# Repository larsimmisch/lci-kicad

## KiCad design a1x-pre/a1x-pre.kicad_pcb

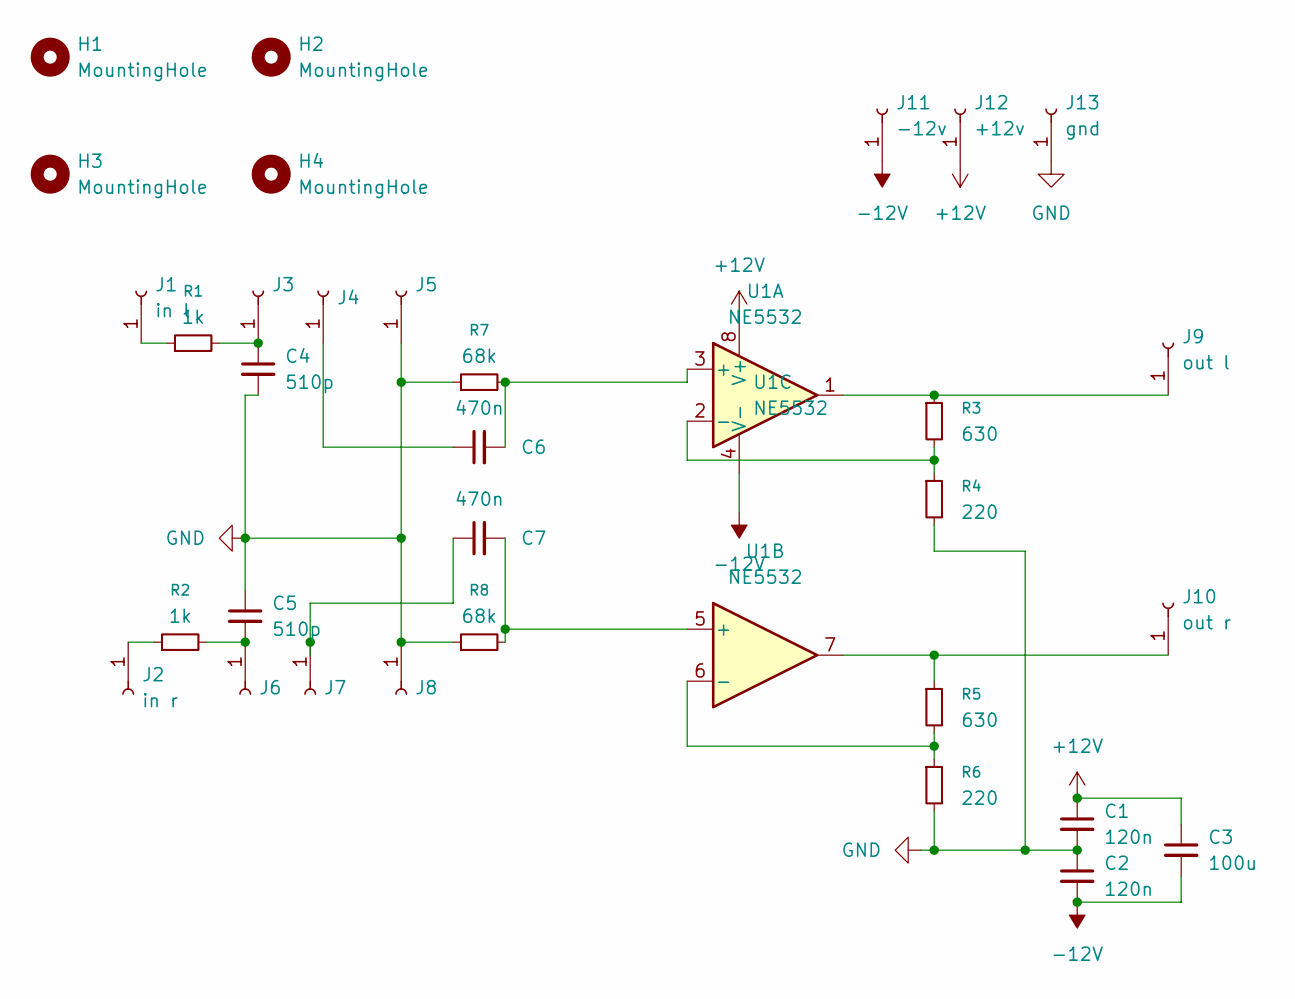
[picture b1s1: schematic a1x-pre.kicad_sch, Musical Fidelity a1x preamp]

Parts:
C1, C2: 120n; C_0201_0603Metric_Pad0.64x0.40mm_HandSolder
C3: 100u; C_0201_0603Metric_Pad0.64x0.40mm_HandSolder
C4, C5: 510p; C_0201_0603Metric_Pad0.64x0.40mm_HandSolder
C6, C7: 470n; C_0201_0603Metric_Pad0.64x0.40mm_HandSolder
H1, H2, H3, H4: MountingHole; MountingHole_3.2mm_M3
J1: in l; PinHeader_1x01_P1.00mm_Vertical
J2: in r; PinHeader_1x01_P1.00mm_Vertical
J3, J4, J5, J6, J7, J8: Conn_01x01_Socket; PinHeader_1x01_P1.00mm_Vertical
J9: out l; PinHeader_1x01_P1.00mm_Vertical
J10: out r; PinHeader_1x01_P1.00mm_Vertical
J11: -12v; PinHeader_1x01_P1.00mm_Vertical
J12: +12v; PinHeader_1x01_P1.00mm_Vertical
J13: gnd; PinHeader_1x01_P1.00mm_Vertical
R1, R2: 1k; R_0201_0603Metric_Pad0.64x0.40mm_HandSolder
R3, R5: 630; R_0201_0603Metric_Pad0.64x0.40mm_HandSolder
R4, R6: 220; R_0201_0603Metric_Pad0.64x0.40mm_HandSolder
R7, R8: 68k; R_0201_0603Metric_Pad0.64x0.40mm_HandSolder
U1: NE5532; SOIC-8_3.9x4.9mm_P1.27mm

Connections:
+12V: C1.1, C3.1, J12.1, U1.8 (V+)
-12V: C2.2, C3.2, J11.1, U1.4 (V-)
GND: C1.2, C2.1, C4.2, C5.1, J5.1, J8.1, J13.1, R4.2, R6.2, R7.1, R8.1
unnamed: J1.1, R1.1
unnamed: J2.1, R2.1
unnamed: C4.1, J3.1, R1.2
unnamed: C6.1, J4.1
unnamed: C5.2, J6.1, R2.2
unnamed: C7.1, J7.1
unnamed: J9.1, R3.1, U1.1
unnamed: J10.1, R5.1, U1.7
unnamed: C6.2, R7.2, U1.3 (+)
unnamed: R3.2, R4.1, U1.2 (-)
unnamed: C7.2, R8.2, U1.5 (+)
unnamed: R5.2, R6.1, U1.6 (-)

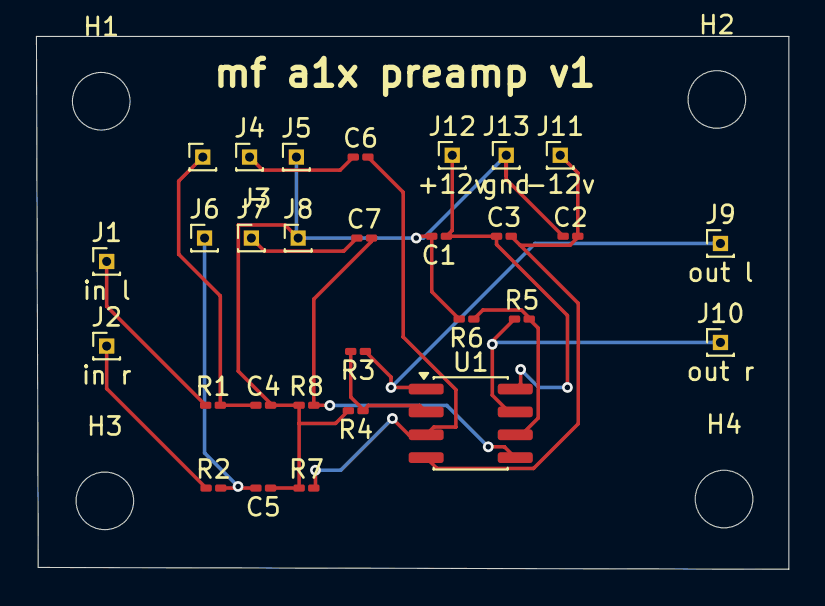
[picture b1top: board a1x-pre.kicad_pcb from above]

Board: 2 copper layers, 41.8 x 29.6 mm, 33 parts (0 on the bottom side), 15 nets.

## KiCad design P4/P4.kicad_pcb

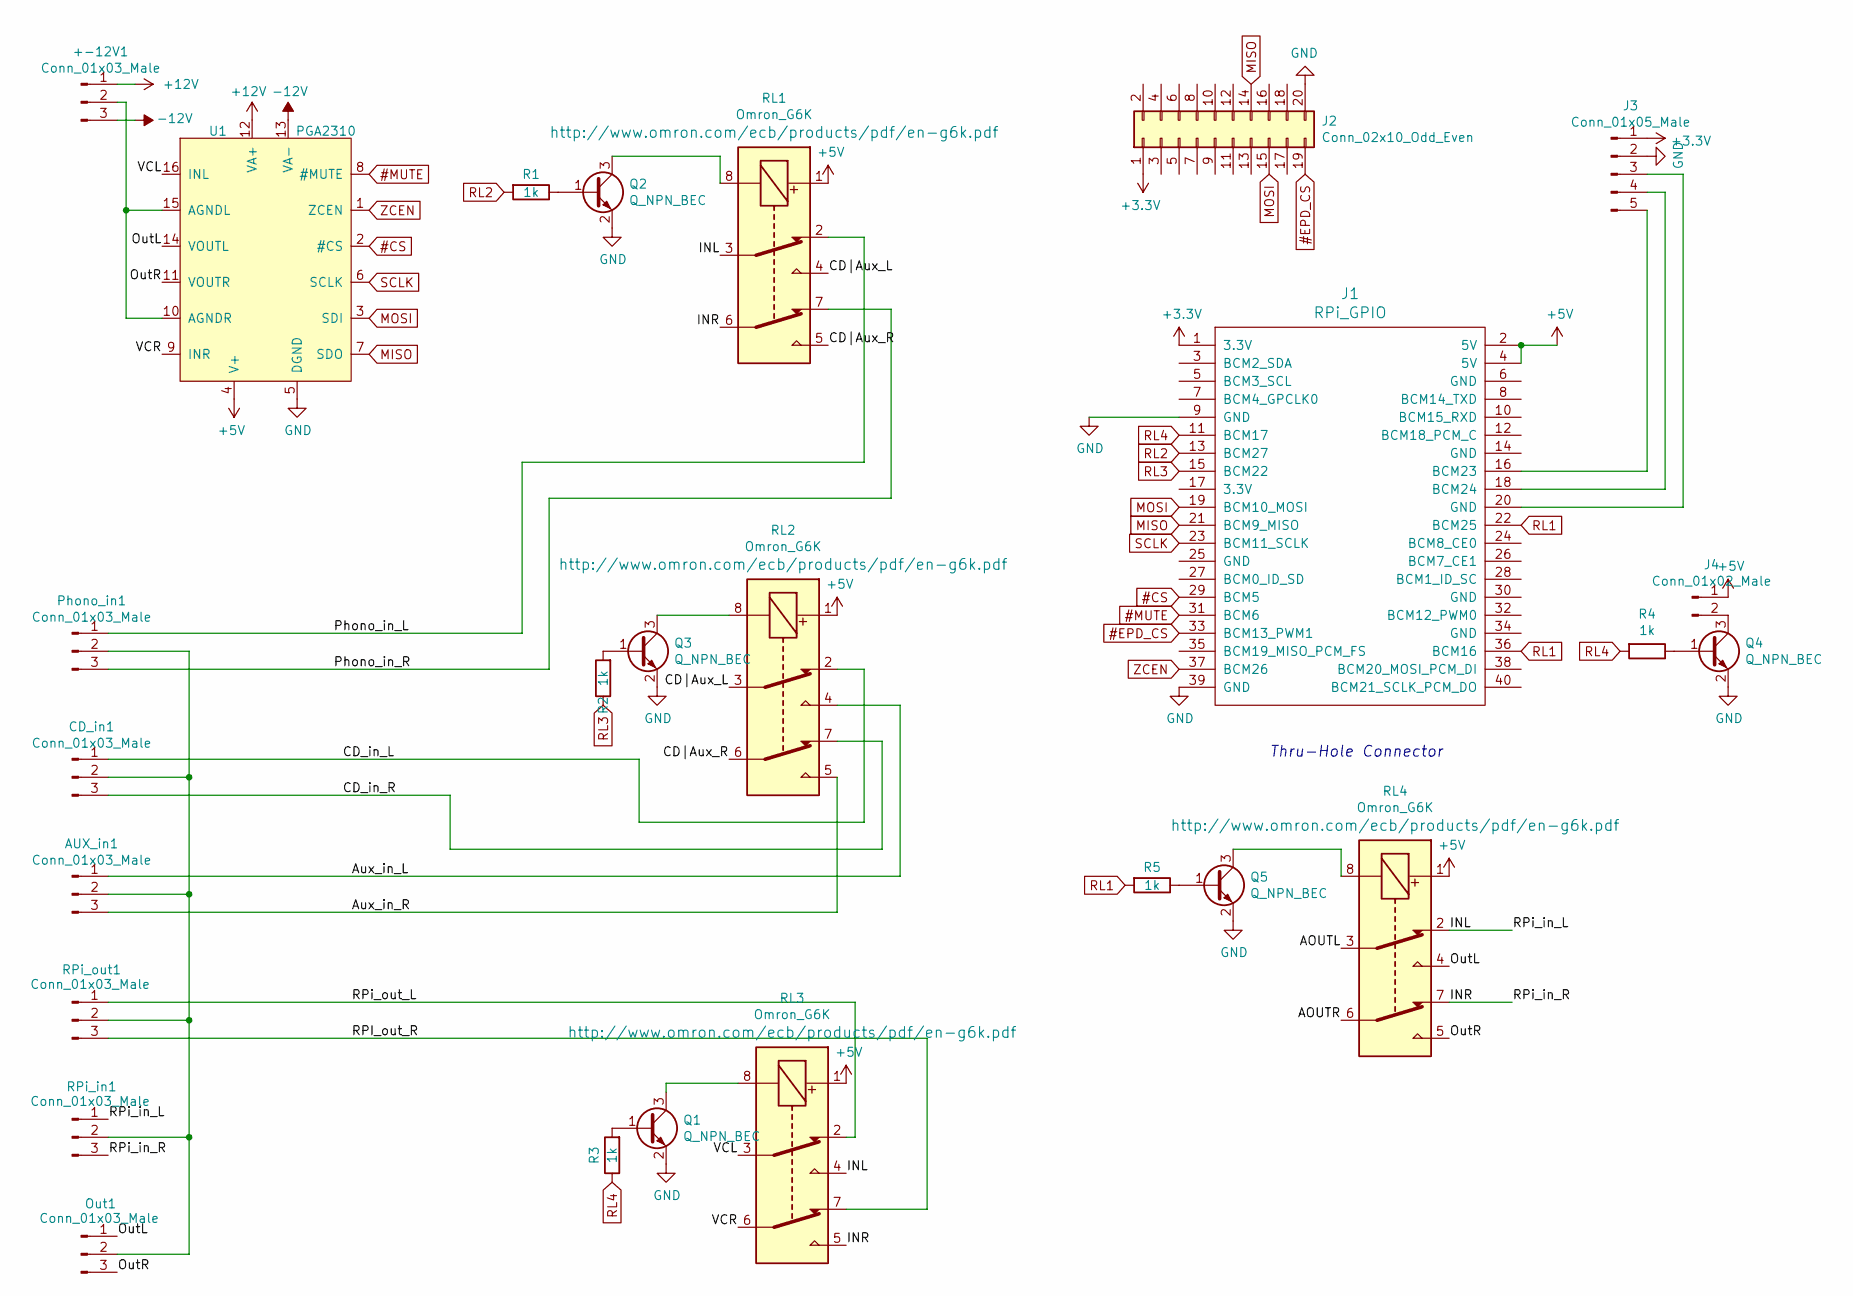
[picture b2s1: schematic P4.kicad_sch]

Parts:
+-12V1: Conn_01x03_Male; PinSocket_1x03_P2.54mm_Vertical
AUX_in1: Conn_01x03_Male; PinSocket_1x03_P2.54mm_Vertical
CD_in1: Conn_01x03_Male; PinSocket_1x03_P2.54mm_Vertical
J1: RPi_GPIO; PinHeader_2x20_P2.54mm_Vertical
J2: Conn_02x10_Odd_Even; PinHeader_2x10_P2.54mm_Vertical
J3: Conn_01x05_Male; PinSocket_1x05_P2.54mm_Vertical
J4: Conn_01x02_Male; PinSocket_1x02_P2.54mm_Vertical
Out1: Conn_01x03_Male; PinSocket_1x03_P2.54mm_Vertical
Phono_in1: Conn_01x03_Male; PinSocket_1x03_P2.54mm_Vertical
Q1, Q2, Q3, Q4, Q5: Q_NPN_BEC; SOT-23W_Handsoldering
R1, R2, R3, R4, R5: 1k; R_0603_1608Metric_Pad0.98x0.95mm_HandSolder
RL1, RL2, RL3, RL4: Omron_G6K; Relay_DPDT_Omron_G6K-2F
RPi_in1: Conn_01x03_Male; PinSocket_1x03_P2.54mm_Vertical
RPi_out1: Conn_01x03_Male; PinSocket_1x03_P2.54mm_Vertical
U1: PGA2310; SOIC-16W_7.5x10.3mm_P1.27mm

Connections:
#CS: J1.29 (BCM5), U1.2 (#CS)
#EPD_CS: J1.33 (BCM13_PWM1), J2.19
#MUTE: J1.31 (BCM6), U1.8 (#MUTE)
+3.3V: J1.1 (3.3V), J2.1, J3.1
+5V: J1.2 (5V), J1.4 (5V), J4.1, RL1.1, RL2.1, RL3.1, RL4.1, U1.4 (V+)
+12V: +-12V1.1, U1.12 (VA+); also elsewhere on the board
-12V: +-12V1.3, U1.13 (VA-); also elsewhere on the board
/AOUTL: RL4.3
/AOUTR: RL4.6
/Aux_in_L: AUX_in1.1, RL2.4
/Aux_in_R: AUX_in1.3, RL2.5
/CD_in_L: CD_in1.1, RL2.2
/CD_in_R: CD_in1.3, RL2.7
/CD|Aux_L: RL1.4, RL2.3
/CD|Aux_R: RL1.5, RL2.6
/INL: RL1.3, RL3.4, RL4.2, RPi_in1.1
/INR: RL1.6, RL3.5, RL4.7, RPi_in1.3
/OutL: Out1.1, RL4.4, U1.14 (VOUTL)
/OutR: Out1.3, RL4.5, U1.11 (VOUTR)
/Phono_in_L: Phono_in1.1, RL1.2
/Phono_in_R: Phono_in1.3, RL1.7
/RPI_out_R: RL3.7, RPi_out1.3
/RPi_out_L: RL3.2, RPi_out1.1
/VCL: RL3.3, U1.16 (INL)
/VCR: RL3.6, U1.9 (INR)
GND: J1.9 (GND), J1.39 (GND), J2.20, J3.2, Q1.2 (E), Q2.2 (E), Q3.2 (E), Q4.2 (E), Q5.2 (E), U1.5 (DGND)
MISO: J1.21 (BCM9_MISO), J2.14, U1.7 (SDO)
MOSI: J1.19 (BCM10_MOSI), J2.15, U1.3 (SDI)
unnamed 28: +-12V1.2, U1.10 (AGNDR), U1.15 (AGNDL); also elsewhere on the board
unnamed: AUX_in1.2, CD_in1.2, Out1.2, Phono_in1.2, RPi_in1.2, RPi_out1.2
unnamed: J1.16 (BCM23), J3.5
unnamed: J1.18 (BCM24), J3.4
unnamed: J1.20 (GND), J3.3
unnamed: J4.2, Q4.3 (C)
unnamed: Q1.1 (B), R3.2
unnamed: Q1.3 (C), RL3.8
unnamed: Q2.1 (B), R1.1
unnamed: Q2.3 (C), RL1.8
unnamed: Q3.1 (B), R2.2
unnamed: Q3.3 (C), RL2.8
unnamed: Q4.1 (B), R4.1
unnamed: Q5.1 (B), R5.1
unnamed: Q5.3 (C), RL4.8
RL1: J1.22 (BCM25), J1.36 (BCM16), R5.2
RL2: J1.13 (BCM27), R1.2
RL3: J1.15 (BCM22), R2.1
RL4: J1.11 (BCM17), R3.1, R4.2
SCLK: J1.23 (BCM11_SCLK), U1.6 (SCLK)
ZCEN: J1.37 (BCM26), U1.1 (ZCEN)

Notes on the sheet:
Thru-Hole Connector

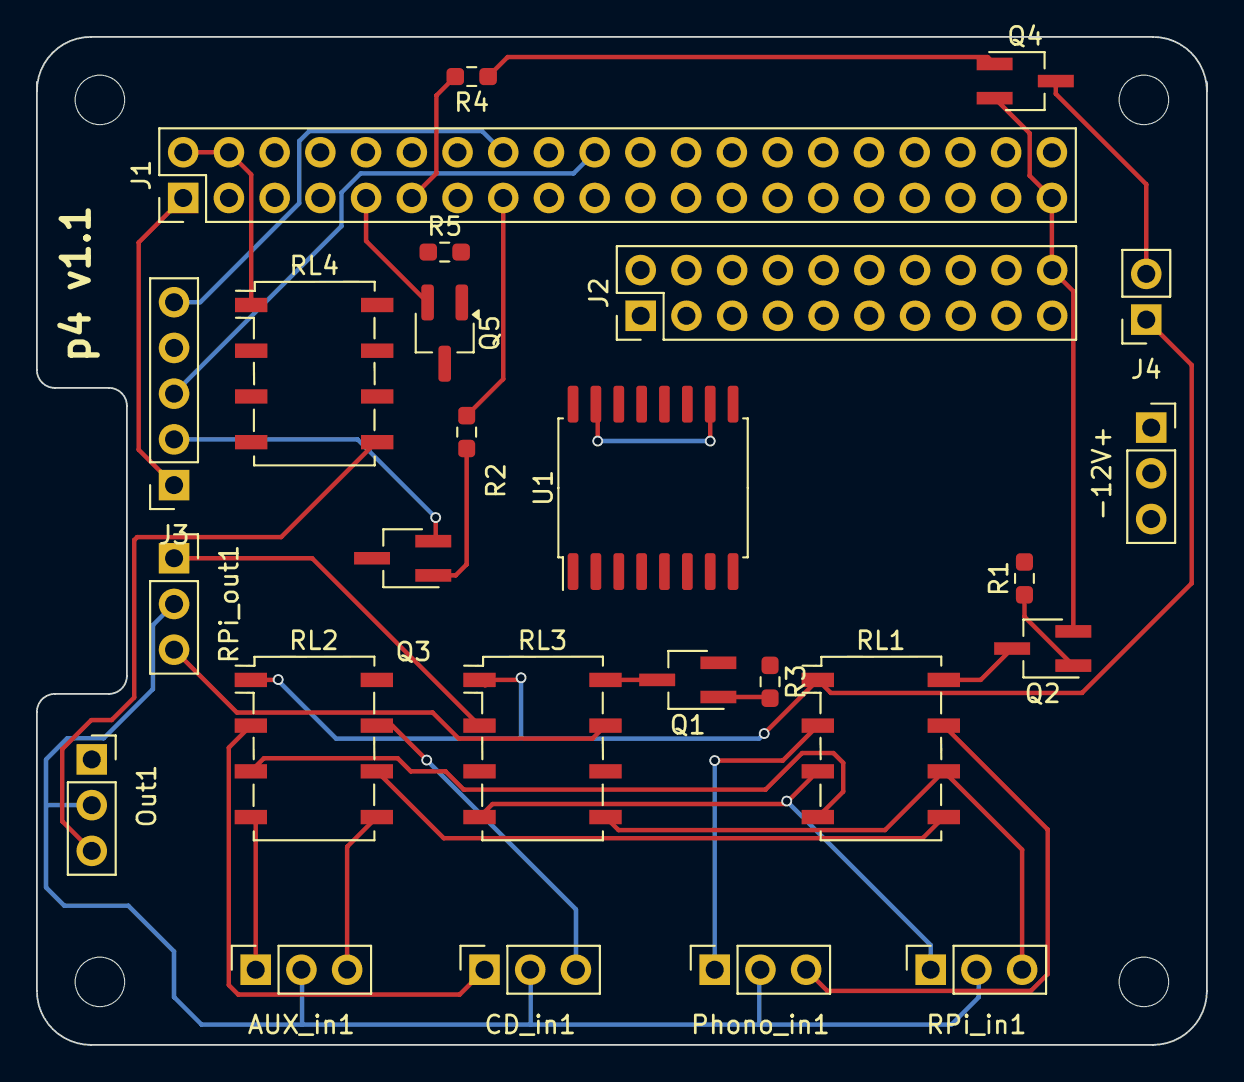
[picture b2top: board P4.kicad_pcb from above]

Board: 2 copper layers, 65.0 x 56.0 mm, 26 parts (0 on the bottom side), 47 nets.

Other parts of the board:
-12V+: Conn_01x03_Male; PinSocket_1x03_P2.54mm_Vertical

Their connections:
+12V: -12V+.1; also elsewhere on the board
-12V: -12V+.3; also elsewhere on the board
unnamed 28: -12V+.2; also elsewhere on the board

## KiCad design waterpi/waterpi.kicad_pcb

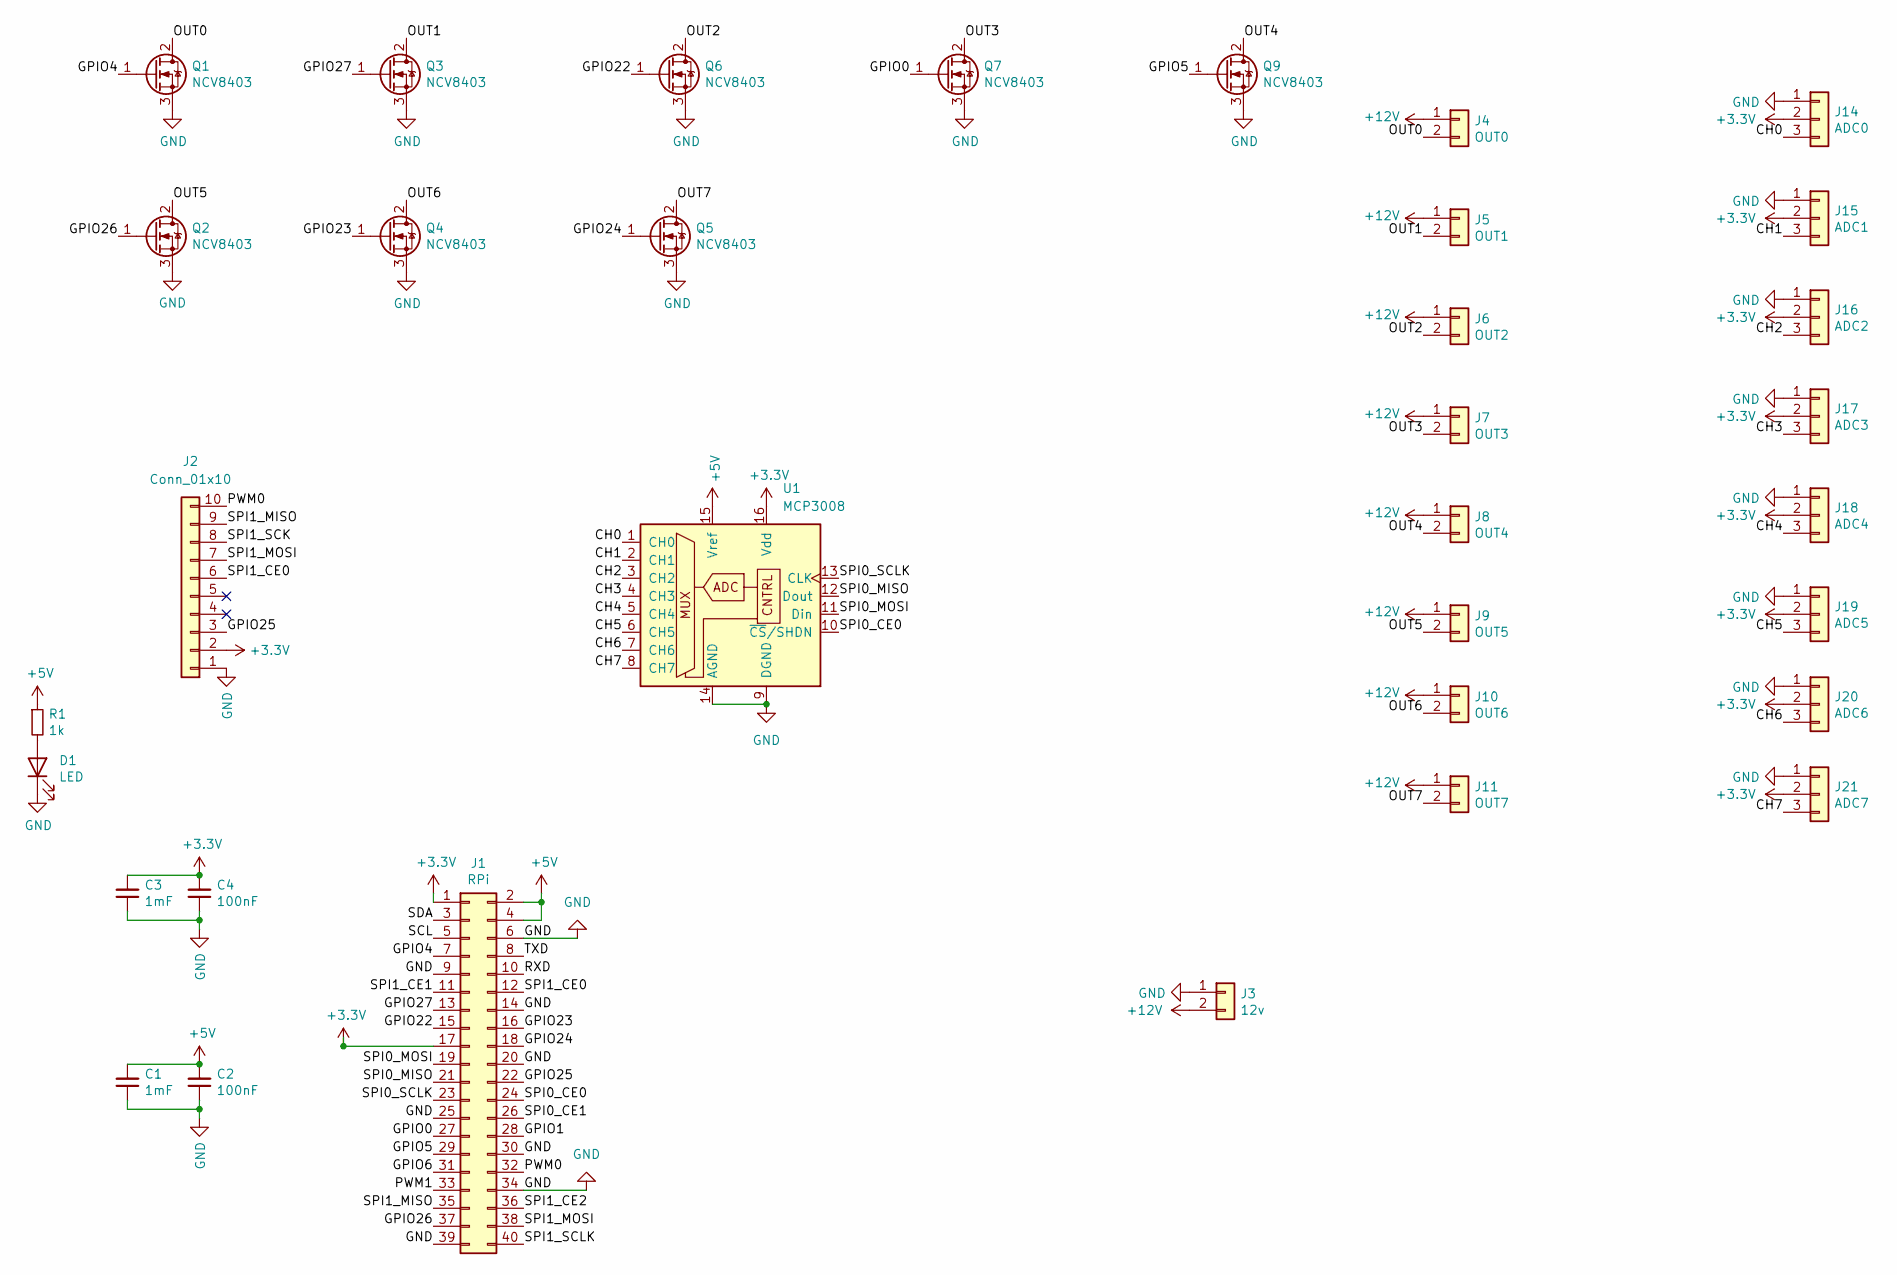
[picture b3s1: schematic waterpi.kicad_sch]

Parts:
C1, C3: 1mF; C_Rect_L4.0mm_W2.5mm_P2.50mm
C2, C4: 100nF; C_0603_1608Metric_Pad1.08x0.95mm_HandSolder
D1: LED; LED_0603_1608Metric_Pad1.05x0.95mm_HandSolder
J1: RPi; PinSocket_2x20_P2.54mm_Vertical
J2: Conn_01x10; PinSocket_1x10_P2.54mm_Vertical
J3: 12v; PinSocket_1x02_P2.54mm_Vertical
J4: OUT0; PinSocket_1x02_P2.54mm_Vertical
J5: OUT1; PinSocket_1x02_P2.54mm_Vertical
J6: OUT2; PinSocket_1x02_P2.54mm_Vertical
J7: OUT3; PinSocket_1x02_P2.54mm_Vertical
J8: OUT4; PinSocket_1x02_P2.54mm_Vertical
J9: OUT5; PinSocket_1x02_P2.54mm_Vertical
J10: OUT6; PinSocket_1x02_P2.54mm_Vertical
J11: OUT7; PinSocket_1x02_P2.54mm_Vertical
J14: ADC0; PinHeader_1x03_P2.54mm_Vertical
J15: ADC1; PinHeader_1x03_P2.54mm_Vertical
J16: ADC2; PinHeader_1x03_P2.54mm_Vertical
J17: ADC3; PinHeader_1x03_P2.54mm_Vertical
J18: ADC4; PinHeader_1x03_P2.54mm_Vertical
J19: ADC5; PinHeader_1x03_P2.54mm_Vertical
J20: ADC6; PinHeader_1x03_P2.54mm_Vertical
J21: ADC7; PinHeader_1x03_P2.54mm_Vertical
Q1, Q2, Q3, Q4, Q5, Q6, Q7, Q9: NCV8403; SOT-223-3_TabPin2
R1: 1k; R_0603_1608Metric_Pad1.05x0.95mm_HandSolder
U1: MCP3008; SO-16_3.9x9.9mm_P1.27mm

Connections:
+3.3V: C3.2, C4.2, J1.1, J1.17, J2.2, J14.2, J15.2, J16.2, J17.2, J18.2, J19.2, J20.2, J21.2, U1.16 (Vdd)
+5V: C1.2, C2.2, J1.2, J1.4, R1.1, U1.15 (Vref)
+12V: J3.2, J4.1, J5.1, J6.1, J7.1, J8.1, J9.1, J10.1, J11.1
/CH0: J14.3, U1.1 (CH0)
/CH1: J15.3, U1.2 (CH1)
/CH2: J16.3, U1.3 (CH2)
/CH3: J17.3, U1.4 (CH3)
/CH4: J18.3, U1.5 (CH4)
/CH5: J19.3, U1.6 (CH5)
/CH6: J20.3, U1.7 (CH6)
/CH7: J21.3, U1.8 (CH7)
/GPIO0: J1.27, Q7.1 (G)
/GPIO1: J1.28
/GPIO4: J1.7, Q1.1 (G)
/GPIO5: J1.29, Q9.1 (G)
/GPIO6: J1.31
/GPIO22: J1.15, Q6.1 (G)
/GPIO23: J1.16, Q4.1 (G)
/GPIO24: J1.18, Q5.1 (G)
/GPIO25: J1.22, J2.3
/GPIO26: J1.37, Q2.1 (G)
/GPIO27: J1.13, Q3.1 (G)
/OUT0: J4.2, Q1.2 (D)
/OUT1: J5.2, Q3.2 (D)
/OUT2: J6.2, Q6.2 (D)
/OUT3: J7.2, Q7.2 (D)
/OUT4: J8.2, Q9.2 (D)
/OUT5: J9.2, Q2.2 (D)
/OUT6: J10.2, Q4.2 (D)
/OUT7: J11.2, Q5.2 (D)
/PWM0: J1.32, J2.10
/PWM1: J1.33
/RXD: J1.10
/SCL: J1.5
/SDA: J1.3
/SPI0_CE0: J1.24, U1.10 (~CS/SHDN)
/SPI0_CE1: J1.26
/SPI0_MISO: J1.21, U1.12 (Dout)
/SPI0_MOSI: J1.19, U1.11 (Din)
/SPI0_SCLK: J1.23, U1.13 (CLK)
/SPI1_CE0: J1.12, J2.6
/SPI1_CE1: J1.11
/SPI1_CE2: J1.36
/SPI1_MISO: J1.35, J2.9
/SPI1_MOSI: J1.38, J2.7
/SPI1_SCK: J2.8
/SPI1_SCLK: J1.40
/TXD: J1.8
GND: C1.1, C2.1, C3.1, C4.1, D1.1 (K), J1.6, J1.9, J1.14, J1.20, J1.25, J1.30, J1.34, J1.39, J2.1, J3.1, J14.1, J15.1, J16.1, J17.1, J18.1, J19.1, J20.1, J21.1, Q1.3 (S), Q2.3 (S), Q3.3 (S), Q4.3 (S), Q5.3 (S), Q6.3 (S), Q7.3 (S), Q9.3 (S), U1.9 (DGND), U1.14 (AGND)
unnamed: D1.2 (A), R1.2

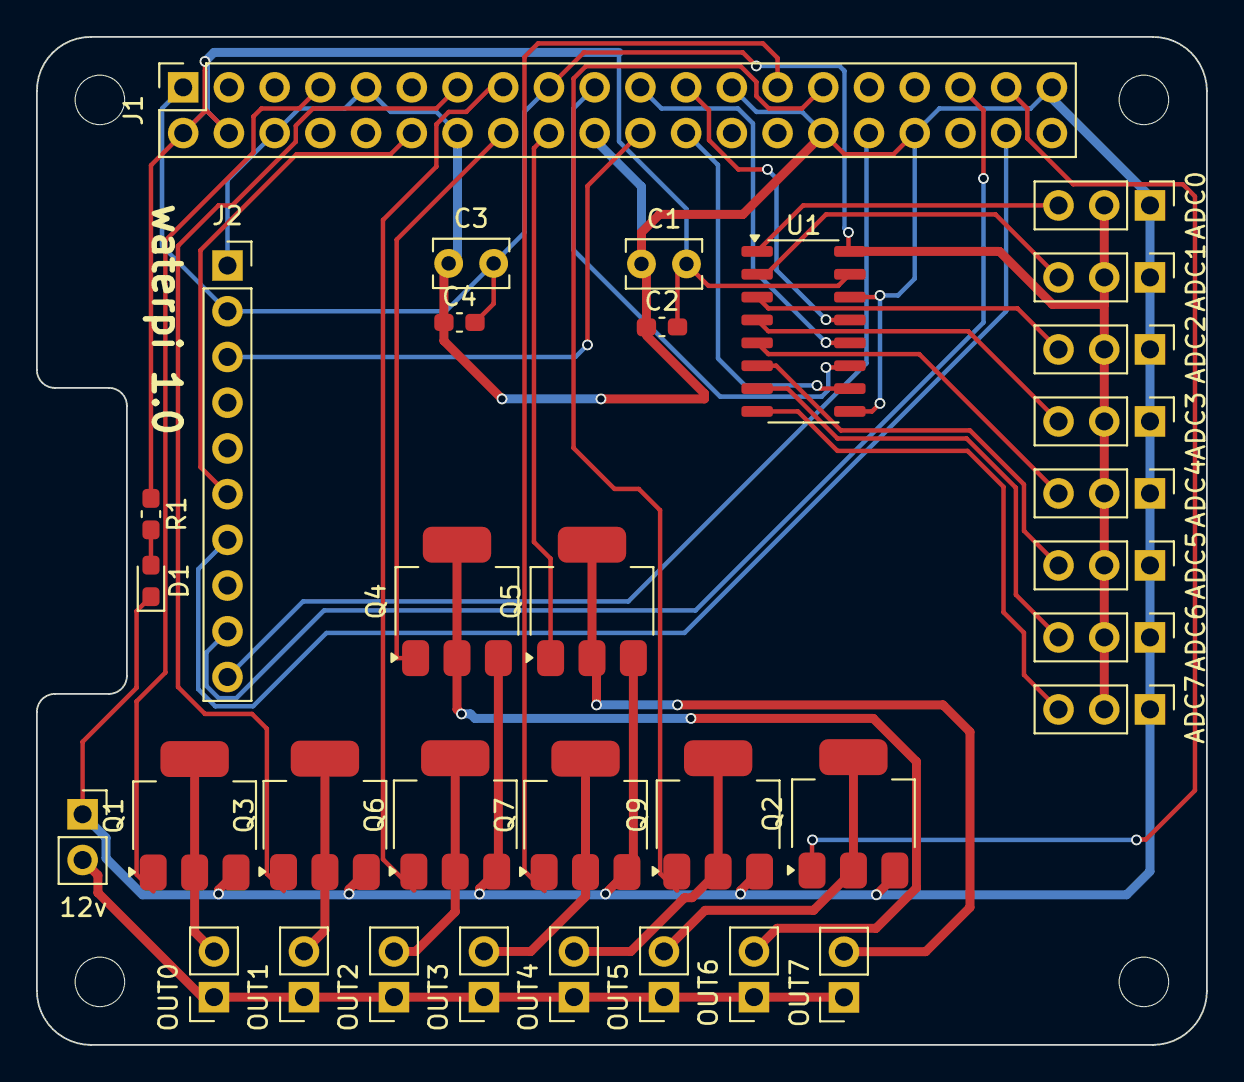
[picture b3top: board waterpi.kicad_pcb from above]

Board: 2 copper layers, 65.0 x 56.0 mm, 34 parts (0 on the bottom side), 38 nets.

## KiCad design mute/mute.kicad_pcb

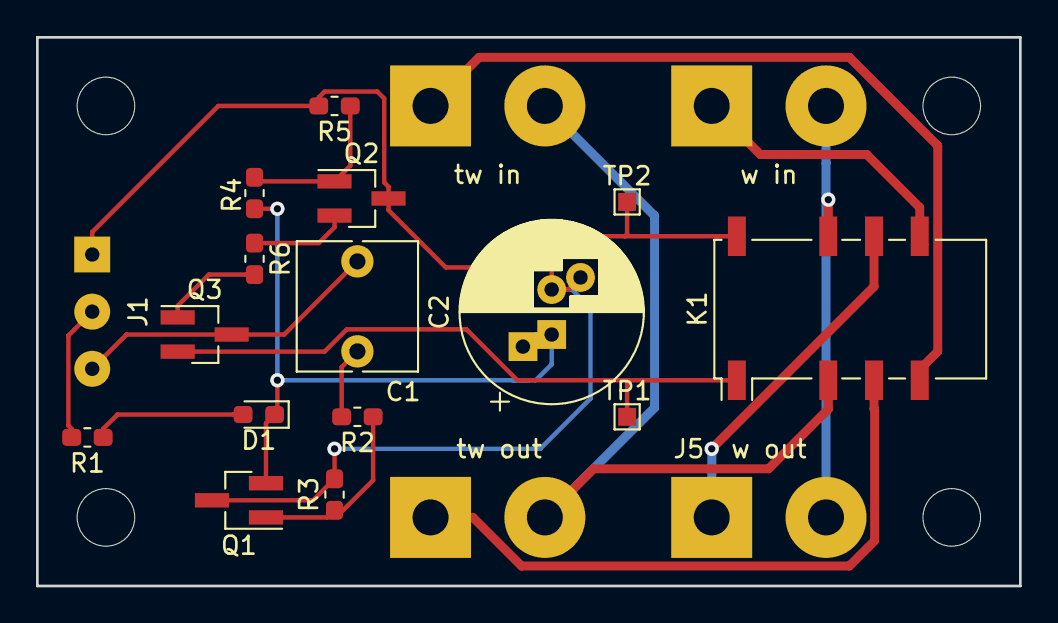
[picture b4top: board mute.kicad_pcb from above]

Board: 2 copper layers, 54.6 x 30.5 mm, 24 parts (0 on the bottom side), 17 nets.

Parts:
C1: 100n; C_Rect_L7.0mm_W6.5mm_P5.00mm
C2: 3.3u; CP_Radial_D10.0mm_P2.50mm_P5.00mm
D1: D; D_0603_1608Metric_Pad1.05x0.95mm_HandSolder
H1, H2, H3, H4: MountingHole; MountingHole_3.2mm_M3_ISO7380
J1: Conn_01x03; SolderWirePad_1x03_P3.175mm_Drill0.8mm
J2: tw in; SolderWirePad_1x02_P7.62mm_Drill2mm
J3: tw out; SolderWirePad_1x02_P7.62mm_Drill2mm
J4: w in; SolderWirePad_1x02_P7.62mm_Drill2mm
J5: w out; SolderWirePad_1x02_P7.62mm_Drill2mm
K1: G6S-2; Relay_DPDT_Omron_G6S-2F
Q1, Q2: npn; SOT-23_Handsoldering
Q3: pnp; SOT-23_Handsoldering
R1, R2, R4, R5, R6: 10k; R_0603_1608Metric_Pad1.05x0.95mm_HandSolder
R3: 100k; R_0603_1608Metric_Pad1.05x0.95mm_HandSolder
TP1, TP2: TestPoint; TestPoint_Pad_1.0x1.0mm

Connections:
/ACSense: J1.2, R1.2
/Aux: K1.1, Q3.2, TP1.1
GND: C2.2, J1.1, K1.12, Q1.3, Q2.3, R3.2, R5.2, TP2.1
unnamed: C1.1, J1.3, Q3.3
unnamed: C1.2, R2.2
unnamed: C2.1, D1.1, Q1.2, R4.2
unnamed: D1.2, R1.1
unnamed: J2.1, K1.5
unnamed: J2.2, J3.2, K1.3
unnamed: J3.1, K1.4
unnamed: J4.1, K1.8
unnamed: J4.2, J5.2, K1.10
unnamed: J5.1, K1.9
unnamed: Q1.1, R2.1, R3.1
unnamed: Q2.1, R4.1, R5.1
unnamed: Q2.2, R6.1
unnamed: Q3.1, R6.2

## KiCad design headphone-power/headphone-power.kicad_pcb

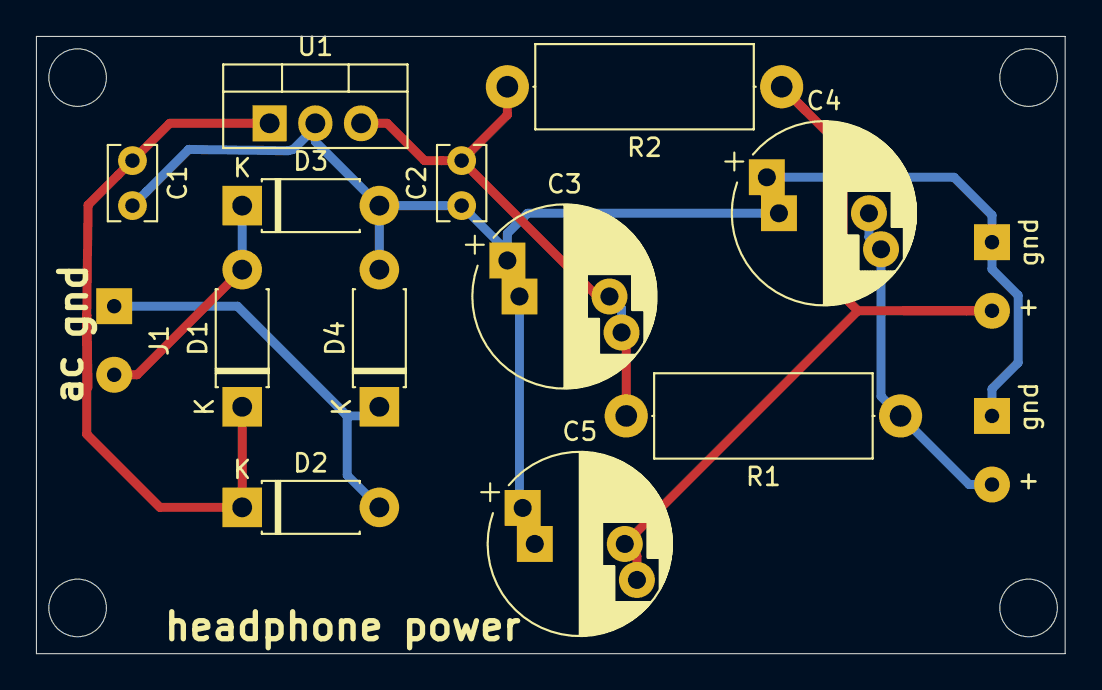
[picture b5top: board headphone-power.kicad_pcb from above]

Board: 2 copper layers, 57.1 x 34.3 mm, 19 parts (0 on the bottom side), 7 nets.

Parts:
C1, C2: 100n; C_Rect_L4.0mm_W2.5mm_P2.50mm
C3, C4, C5: 4700u; CP_Radial_D10.0mm_P5.00mm_P7.50mm
D1, D2, D3, D4: D; D_DO-41_SOD81_P7.62mm_Horizontal
H1, H2, H3, H4: MountingHole; MountingHole_3.2mm_M3
J1, J2, J3: Conn_01x02_Female; SolderWirePad_1x02_P3.81mm_Drill0.8mm
R1, R2: 10; R_Axial_DIN0414_L11.9mm_D4.5mm_P15.24mm_Horizontal
U1: LM7815_TO220; TO-220-3_Vertical

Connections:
AC: D1.2, D3.1, J1.2
GND: D2.2, D4.1, J1.1
unnamed: C1.1, D1.1, D2.1, U1.1
unnamed: C1.2, C2.1, C3.1, C4.1, C5.1, D3.2, D4.2, J2.1, J3.1, U1.2
unnamed: C2.2, C3.2, R1.2, R2.2, U1.3
unnamed: C4.2, J3.2, R1.1
unnamed: C5.2, J2.2, R2.1

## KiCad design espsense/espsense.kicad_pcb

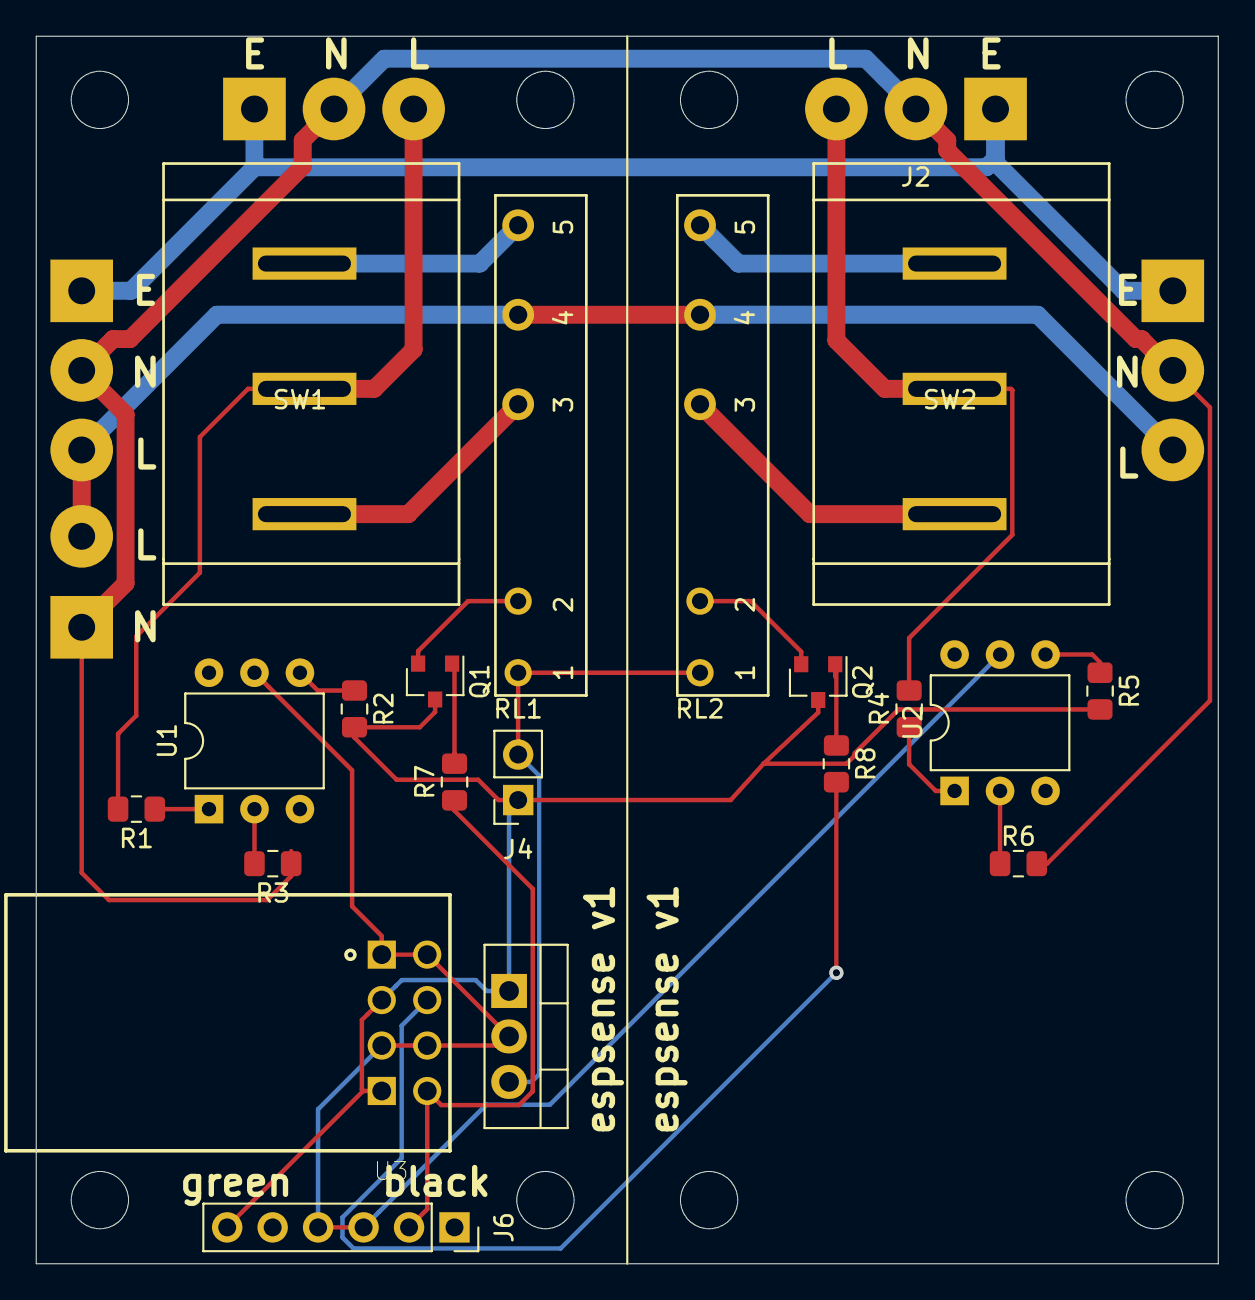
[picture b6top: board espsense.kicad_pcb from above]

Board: 2 copper layers, 66.0 x 68.6 mm, 33 parts (0 on the bottom side), 24 nets.

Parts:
H1, H2, H3, H4, H5, H6, H7, H8: MountingHole; MountingHole_3.2mm_M3
J1, J2, J5, J7: Conn_01x03_Female; SolderWirePad_1x03_P4.445mm_Drill1.5mm
J3: Conn_01x02_Female; SolderWirePad_1x02_P5.08mm_Drill1.5mm
J4: Conn_01x02_Female; PinSocket_1x02_P2.54mm_Vertical
J6: Conn_01x06_Male; PinSocket_1x06_P2.54mm_Vertical
Q1, Q2: Q_NPN_BCE; SOT-23
R1, R3, R4, R6: 47k; R_0805_2012Metric_Pad1.15x1.40mm_HandSolder
R2, R5: 10k; R_0805_2012Metric_Pad1.15x1.40mm_HandSolder
R7, R8: 1k; R_0805_2012Metric_Pad1.15x1.40mm_HandSolder
RL1, RL2: FTR-LYCA
SW1, SW2: SW_SPDT; SW-Marquard_1843.1201
U1, U2: H11AA1; DIP-6_W7.62mm
U3: ESP8266-01_ESP-01; XCVR_ESP8266-01_ESP-01
U4: LD1117S12TR_SOT223; TO-220-3_Vertical

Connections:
+3V3: J6.3, J6.4, U1.5, U2.5, U3.1, U3.3, U3.6, U3.8, U4.2
+5V: J4.2, RL1.1, RL2.1, U4.3
/SW1: J1.3, R1.2, SW1.2
/SW2: J2.3, R4.2, SW2.2
/TXD: J6.2, R7.1, U3.5
AC: J3.2, J5.3, J7.3, RL1.4, RL2.4
Earth_Protective: J1.1, J2.1, J5.1, J7.1
GND: J1.2, J2.2, J3.1, J5.2, J7.2, R3.1, R6.1
GNDD: J4.1, J6.6, Q1.3, Q2.3, R2.2, R5.2, U3.2, U3.4, U4.1
unnamed: Q1.1, R7.2
unnamed: Q1.2, RL1.2
unnamed: Q2.1, R8.1
unnamed: Q2.2, RL2.2
unnamed: R1.1, U1.1
unnamed: R2.1, U1.4
unnamed: R3.2, U1.2
unnamed: R4.1, U2.1
unnamed: R5.1, U2.4
unnamed: R6.2, U2.2
unnamed: R8.2, U3.7
unnamed: RL1.3, SW1.3
unnamed: RL1.5, SW1.1
unnamed: RL2.3, SW2.3
unnamed: RL2.5, SW2.1

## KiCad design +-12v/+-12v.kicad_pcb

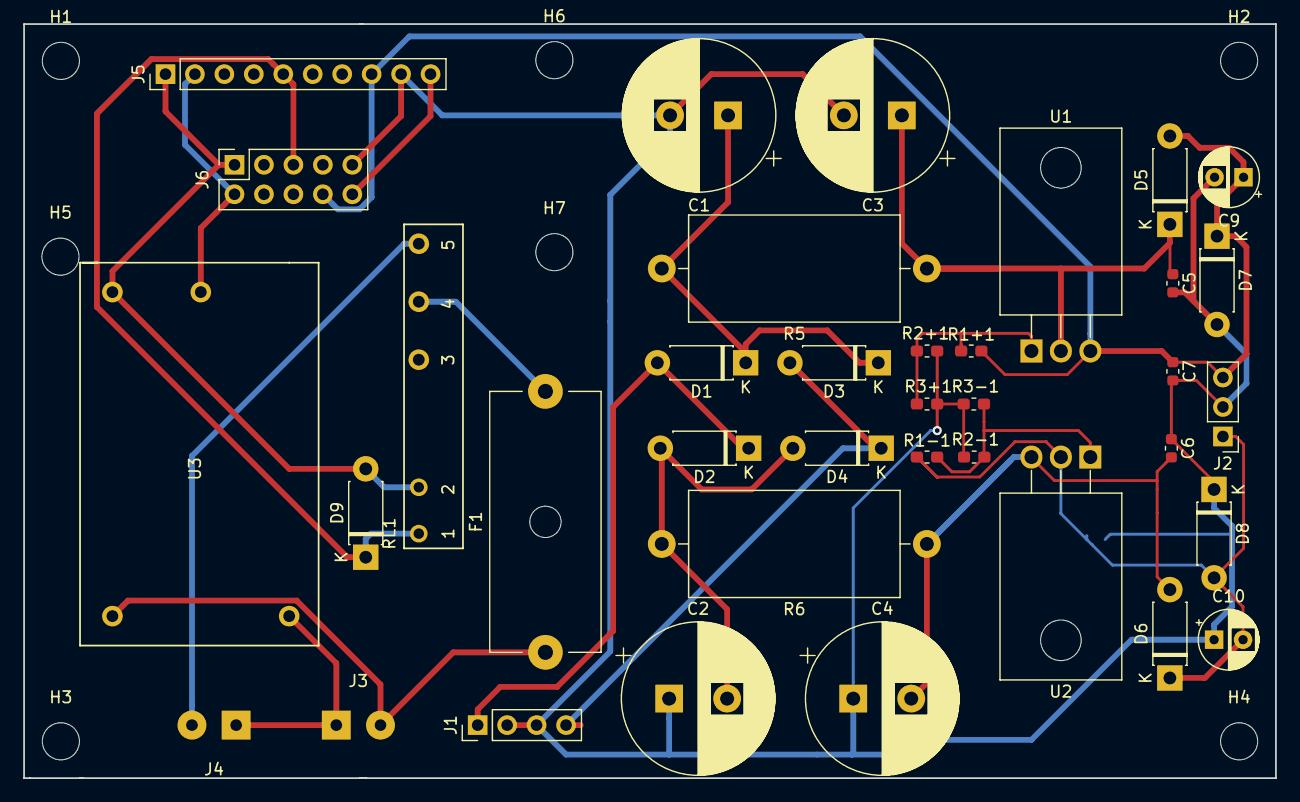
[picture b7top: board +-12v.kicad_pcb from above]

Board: 2 copper layers, 108.0 x 65.0 mm, 45 parts (1 on the bottom side), 18 nets.

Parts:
C1, C2, C3, C4: 2u2; CP_Radial_D13.0mm_P5.00mm
C5, C6, C7, C8: 100n; C_0603_1608Metric
C9, C10: 10u; CP_Radial_D5.0mm_P2.50mm
D1, D2, D3, D4, D5, D6, D7, D8, D9: D_Small; D_DO-41_SOD81_P7.62mm_Horizontal
F1: Fuse; Fuseholder_Cylinder-5x20mm_Schurter_0031_8201_Horizontal_Op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
H1, H2, H3, H4, H5, H6, H7: MountingHole; MountingHole_3.2mm_M3_DIN965
J1: Conn_01x04_Male; PinHeader_1x04_P2.54mm_Vertical
J2: Conn_01x03_Male; PinHeader_1x03_P2.54mm_Vertical
J3, J4: Screw_Terminal_01x02; SolderWirePad_1x02_P3.81mm_Drill1mm
J5: Conn_01x10; PinHeader_1x10_P2.54mm_Vertical
J6: Conn_02x05_Odd_Even; PinSocket_2x05_P2.54mm_Vertical
R1+1, R1-1: 390; R_0603_1608Metric_Pad1.05x0.95mm_HandSolder
R2+1, R2-1: 3k3; R_0603_1608Metric_Pad1.05x0.95mm_HandSolder
R3+1, R3-1: opt; R_0603_1608Metric_Pad1.05x0.95mm_HandSolder
R5, R6: 4R7; R_Axial_DIN0918_L18.0mm_D9.0mm_P22.86mm_Horizontal
RL1: FTR-LYCA
U1: LM317_TO3; TO-220F-3_Horizontal_TabDown
U2: LM337_TO3; TO-220F-3_Horizontal_TabDown
U3: RECOM_RAC02-05SC

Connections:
/+5v: J5.2, J6.2, U3.2
/+12v: C7.1, C9.1, D5.2, D7.1, J2.3, J5.8, J6.8, R1+1.2, U1.3
/-12v: C8.2, C10.2, D6.1, D8.2, J2.1, J5.10, J6.10, R1-1.1, U2.2
/DGND: D9.2, J5.1, J6.1, RL1.2, U3.1
/GND: C1.2, C2.1, C3.2, C4.1, C5.2, C6.1, C7.2, C8.1, C9.2, C10.1, D7.2, D8.1, J1.2, J1.3, J2.2, J5.9, J6.9, R2+1.1, R2-1.2, R3+1.1, R3-1.2
unnamed: C1.1, D1.1, D3.1, R5.2
unnamed: C2.2, D2.2, D4.2, R6.2
unnamed: C3.1, C5.1, D5.1, R5.1, U1.2
unnamed: C4.2, C6.2, D6.2, R6.1, U2.3
unnamed: D1.2, D2.1, J1.1
unnamed: D3.2, D4.1, J1.4
unnamed: D9.1, J5.5, J6.5, RL1.1
unnamed: F1.1, J3.2, U3.4
unnamed: F1.2, RL1.4
unnamed: J3.1, J4.1, U3.3
unnamed: J4.2, RL1.5
unnamed: R1+1.1, R2+1.2, R3+1.2, U1.1
unnamed: R1-1.2, R2-1.1, R3-1.1, U2.1
